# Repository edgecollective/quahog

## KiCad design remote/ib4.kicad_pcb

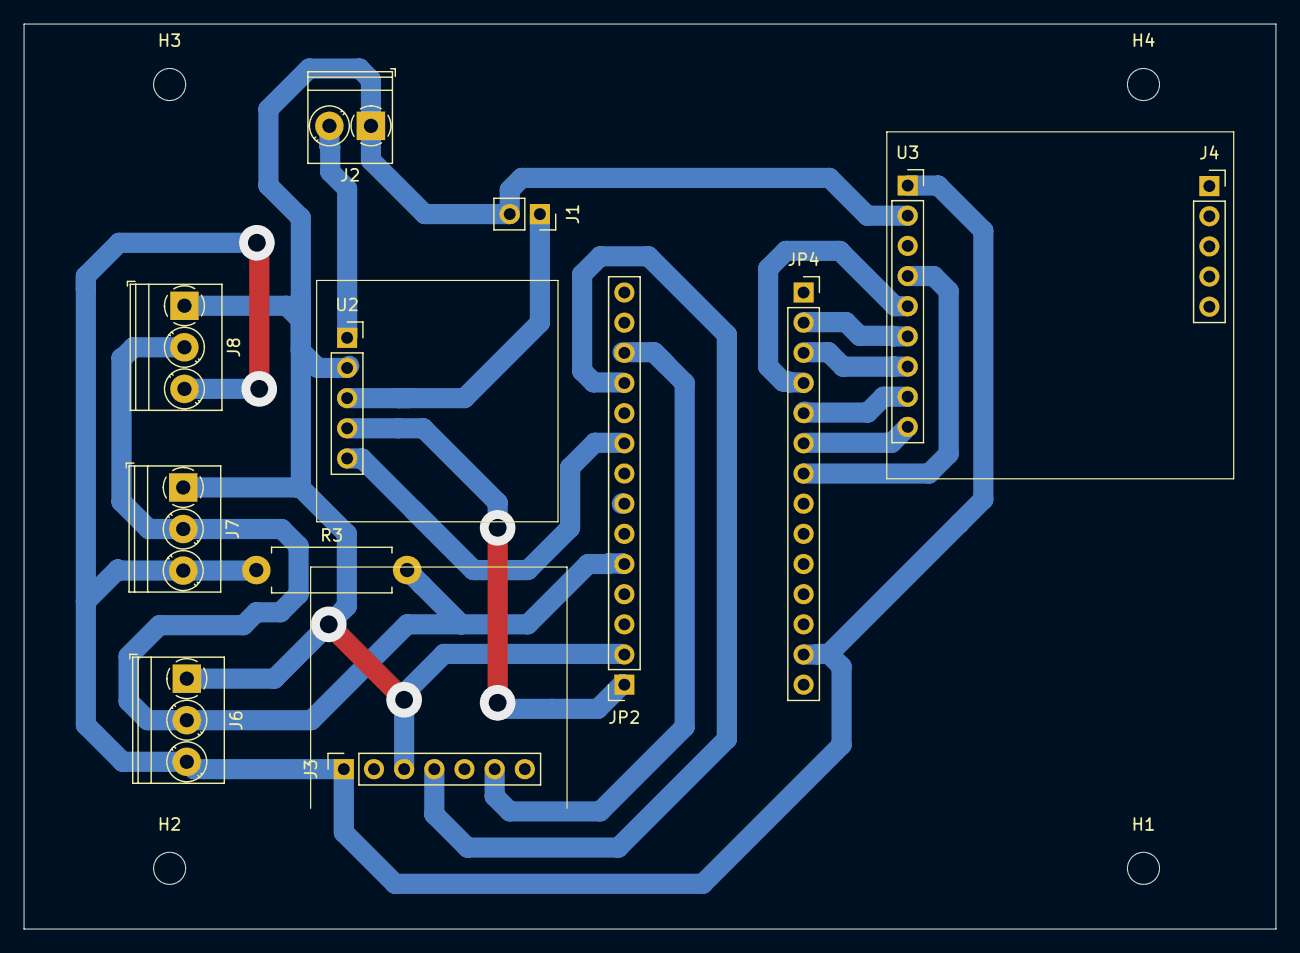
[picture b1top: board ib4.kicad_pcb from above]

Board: 4 copper layers, 105.4 x 76.2 mm, 16 parts (0 on the bottom side), 15 nets.

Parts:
H1, H2, H3, H4: MountingHole; MountingHole_2.7mm_M2.5
J1: Conn_01x02_Female; PinSocket_1x02_P2.54mm_Vertical
J2: Screw_Terminal_01x02; TerminalBlock_Phoenix_PT-1,5-2-3.5-H_1x02_P3.50mm_Horizontal
J3: Conn_01x07_Female; PinSocket_1x07_P2.54mm_Vertical
J4: Conn_01x05_Female; PinSocket_1x05_P2.54mm_Vertical
J6, J7, J8: Screw_Terminal_01x03; TerminalBlock_Phoenix_PT-1,5-3-3.5-H_1x03_P3.50mm_Horizontal
JP2, JP4: HEADER-1X14; PinSocket_1x14_P2.54mm_Vertical
R3: R; R_Axial_DIN0411_L9.9mm_D3.6mm_P12.70mm_Horizontal
U2: tpl5110; PinSocket_1x05_P2.54mm_Vertical
U3: lora_breakout; PinSocket_1x09_P2.54mm_Vertical

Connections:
+3V3: J3.1, J6.3, J7.3, J8.3, JP4.13, R3.1, U3.1
D12: J6.2, J7.2, J8.2, JP2.5, R3.2
DONE: JP2.9, U2.5
G0: JP4.7, U3.4
GND: J1.2, J2.1, J3.3, J6.1, J7.1, J8.1, JP2.2, U2.2, U3.2
LI-ION: J2.2, U2.1
LORA_CS: JP4.5, U3.8
LORA_RST: JP4.6, U3.9
MISO: JP4.2, U3.6
MOSI: JP4.3, U3.7
unnamed: J1.1, U2.3
SCK: JP4.4, U3.5
SCL: J3.4, JP2.11
SDA: J3.6, JP2.12
TIMED_POWER: JP2.1, U2.4
